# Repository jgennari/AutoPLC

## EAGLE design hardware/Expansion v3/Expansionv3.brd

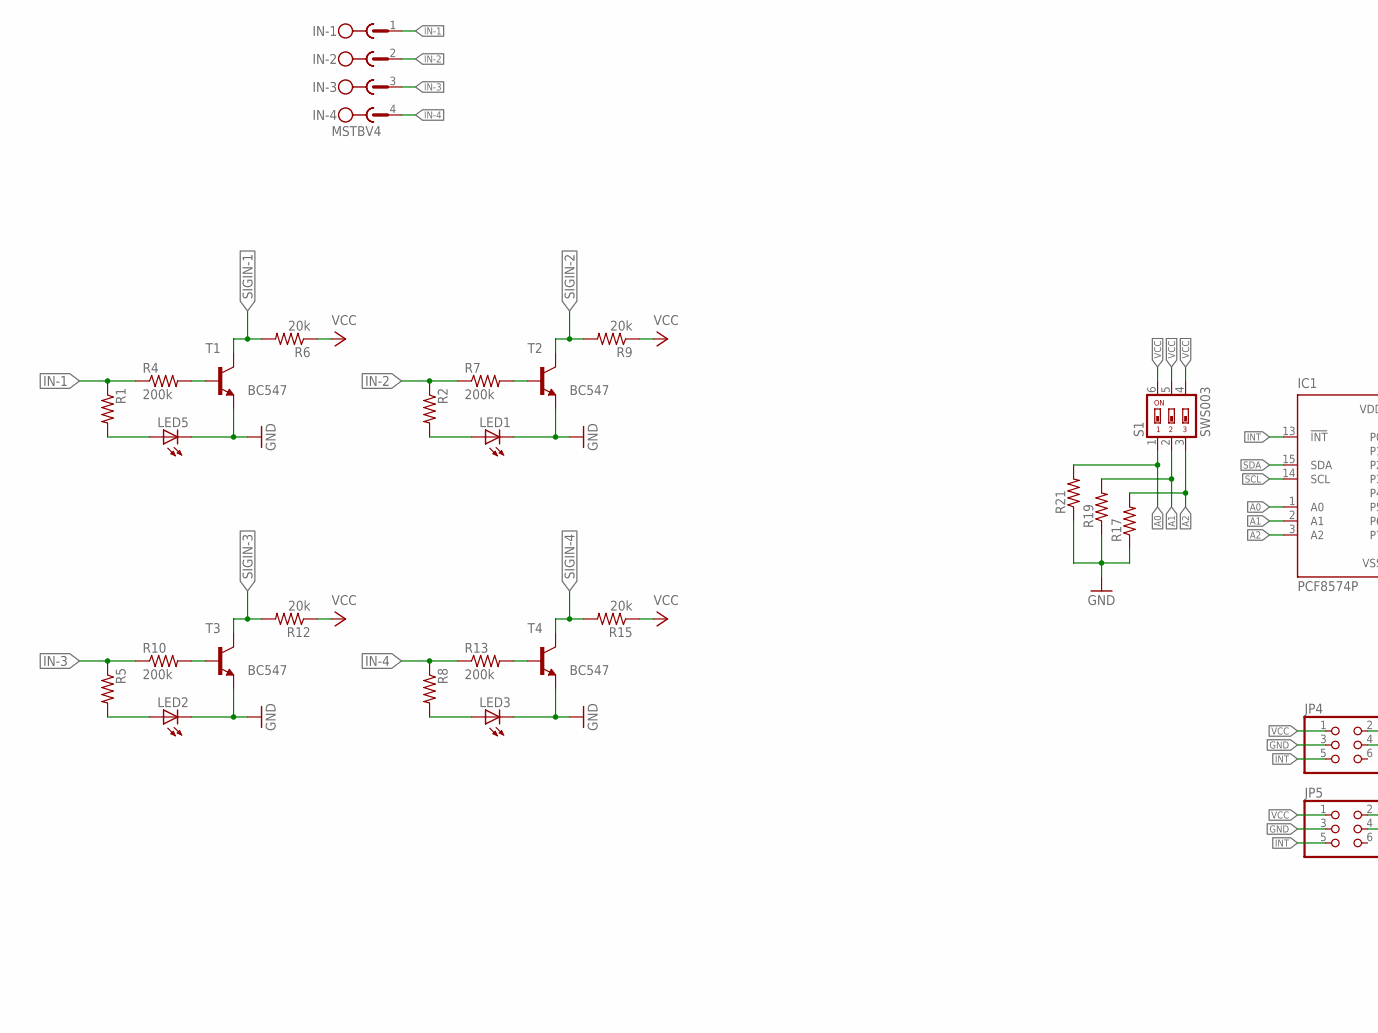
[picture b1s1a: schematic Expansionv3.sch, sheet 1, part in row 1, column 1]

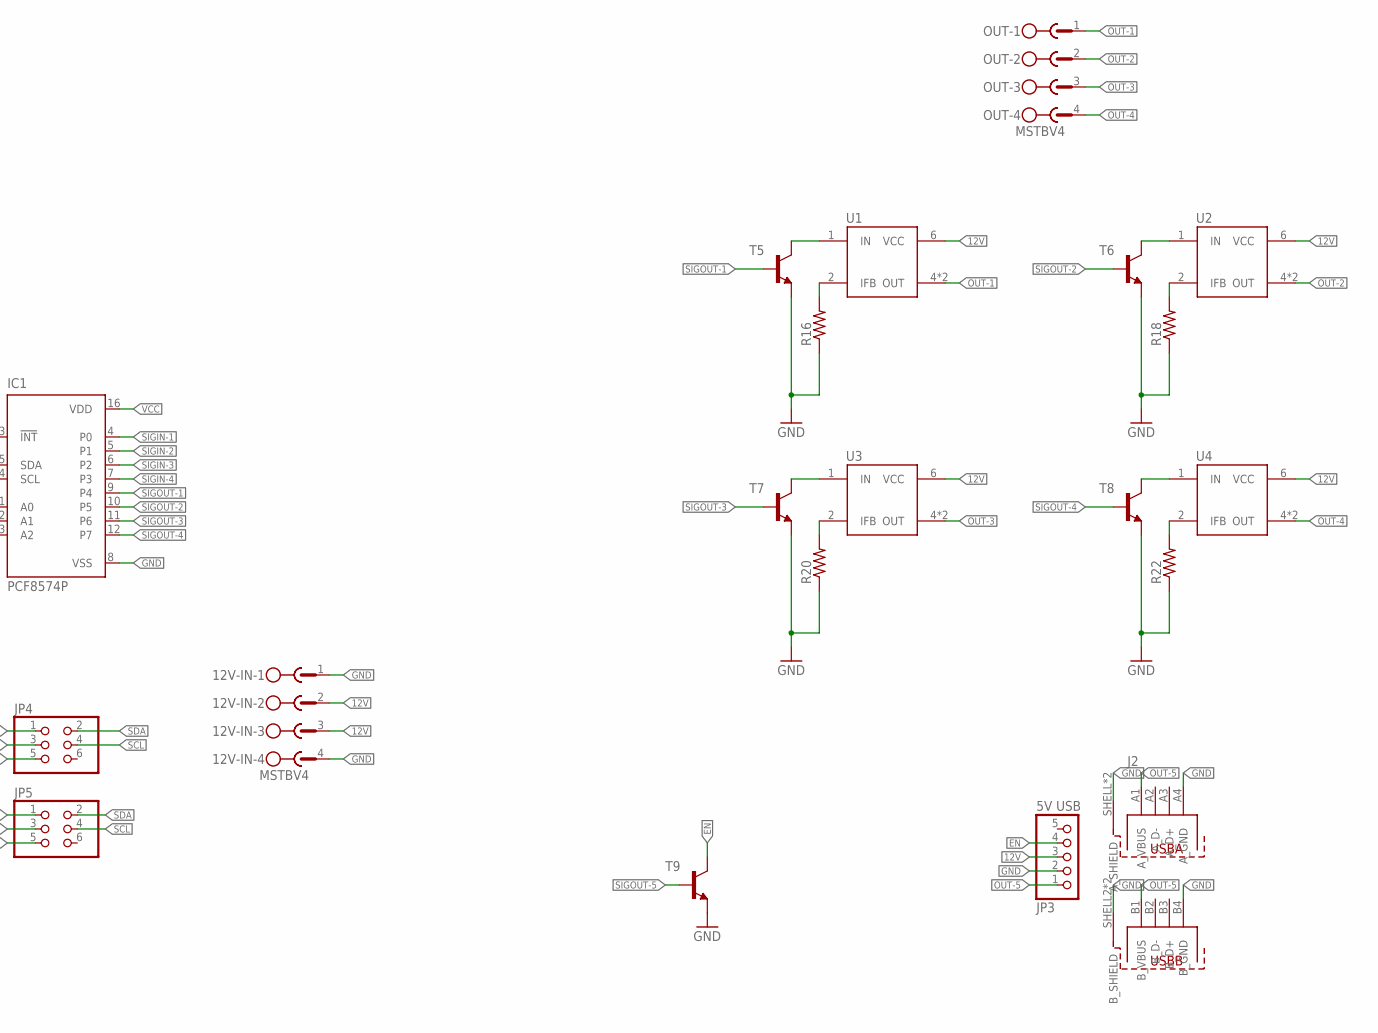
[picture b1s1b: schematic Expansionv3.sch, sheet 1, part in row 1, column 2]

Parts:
12V-IN: MSTBV4
IC1: PCF8574P; DIL16
IN: MSTBV4
J2: 614008235023
JP3: 5V USB; 1X05
JP4, JP5: PINHD-2X3; 2X03
LED1, LED2, LED3, LED5: LEDCHIPLED_0805; CHIPLED_0805
OUT: MSTBV4
R1, R2, R5, R8, R16, R17, R18, R19, R20, R21, R22: R-US_R0805; R0805
R4, R7, R10, R13: 200k; R0805
R6, R9, R12, R15: 20k; R0805
S1: SWS003; SMS-003
T1, T2, T3, T4: BC547; SOT23-EBC
T5, T6, T7, T8, T9: -NPN-SOT23-EBC; SOT23-EBC
U1, U2, U3, U4: IR3315; TO263-5

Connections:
12V: 12V-IN.2, 12V-IN.3, JP3.3, U1.6 (VCC), U2.6 (VCC), U3.6 (VCC), U4.6 (VCC)
A0: IC1.1 (A0), R21.2, S1.1
A1: IC1.2 (A1), R19.2, S1.2
A2: IC1.3 (A2), R17.2, S1.3
EN: JP3.4, T9.C
GND: 12V-IN.1, 12V-IN.4, IC1.8 (VSS), J2.A4 (A_GND), J2.B4 (B_GND), J2.SHELL (A_SHIELD), J2.SHELL1 (A_SHIELD), J2.SHELL2 (B_SHIELD), J2.SHELL3 (B_SHIELD), JP3.2, JP4.3, JP5.3, LED1.C, LED2.C, LED3.C, LED5.C, R16.1, R17.1, R18.1, R19.1, R20.1, R21.1, R22.1, T1.E, T2.E, T3.E, T4.E, T5.E, T6.E, T7.E, T8.E, T9.E
IN-1: IN.1, R1.1, R4.1
IN-2: IN.2, R2.1, R7.1
IN-3: IN.3, R5.1, R10.1
IN-4: IN.4, R8.1, R13.1
INT: IC1.13 (!INT), JP4.5, JP5.5
unnamed: LED5.A, R1.2
unnamed: R4.2, T1.B
unnamed: LED1.A, R2.2
unnamed: R7.2, T2.B
unnamed: LED2.A, R5.2
unnamed: R10.2, T3.B
unnamed: LED3.A, R8.2
unnamed: R13.2, T4.B
unnamed: T5.C, U1.1 (IN)
unnamed: R16.2, U1.2 (IFB)
unnamed: T6.C, U2.1 (IN)
unnamed: R18.2, U2.2 (IFB)
unnamed: T7.C, U3.1 (IN)
unnamed: R20.2, U3.2 (IFB)
unnamed: T8.C, U4.1 (IN)
unnamed: R22.2, U4.2 (IFB)
OUT-1: OUT.1, U1.4 (OUT), U1.5 (OUT)
OUT-2: OUT.2, U2.4 (OUT), U2.5 (OUT)
OUT-3: OUT.3, U3.4 (OUT), U3.5 (OUT)
OUT-4: OUT.4, U4.4 (OUT), U4.5 (OUT)
OUT-5: J2.A1 (A_VBUS), J2.B1 (B_VBUS), JP3.1
SCL: IC1.14 (SCL), JP4.4, JP5.4
SDA: IC1.15 (SDA), JP4.2, JP5.2
SIGIN-1: IC1.4 (P0), R6.2, T1.C
SIGIN-2: IC1.5 (P1), R9.2, T2.C
SIGIN-3: IC1.6 (P2), R12.2, T3.C
SIGIN-4: IC1.7 (P3), R15.2, T4.C
SIGOUT-1: IC1.9 (P4), T5.B
SIGOUT-2: IC1.10 (P5), T6.B
SIGOUT-3: IC1.11 (P6), T7.B
SIGOUT-4: IC1.12 (P7), T8.B
SIGOUT-5: T9.B
VCC: IC1.16 (VDD), JP4.1, JP5.1, R6.1, R9.1, R12.1, R15.1, S1.4, S1.5, S1.6

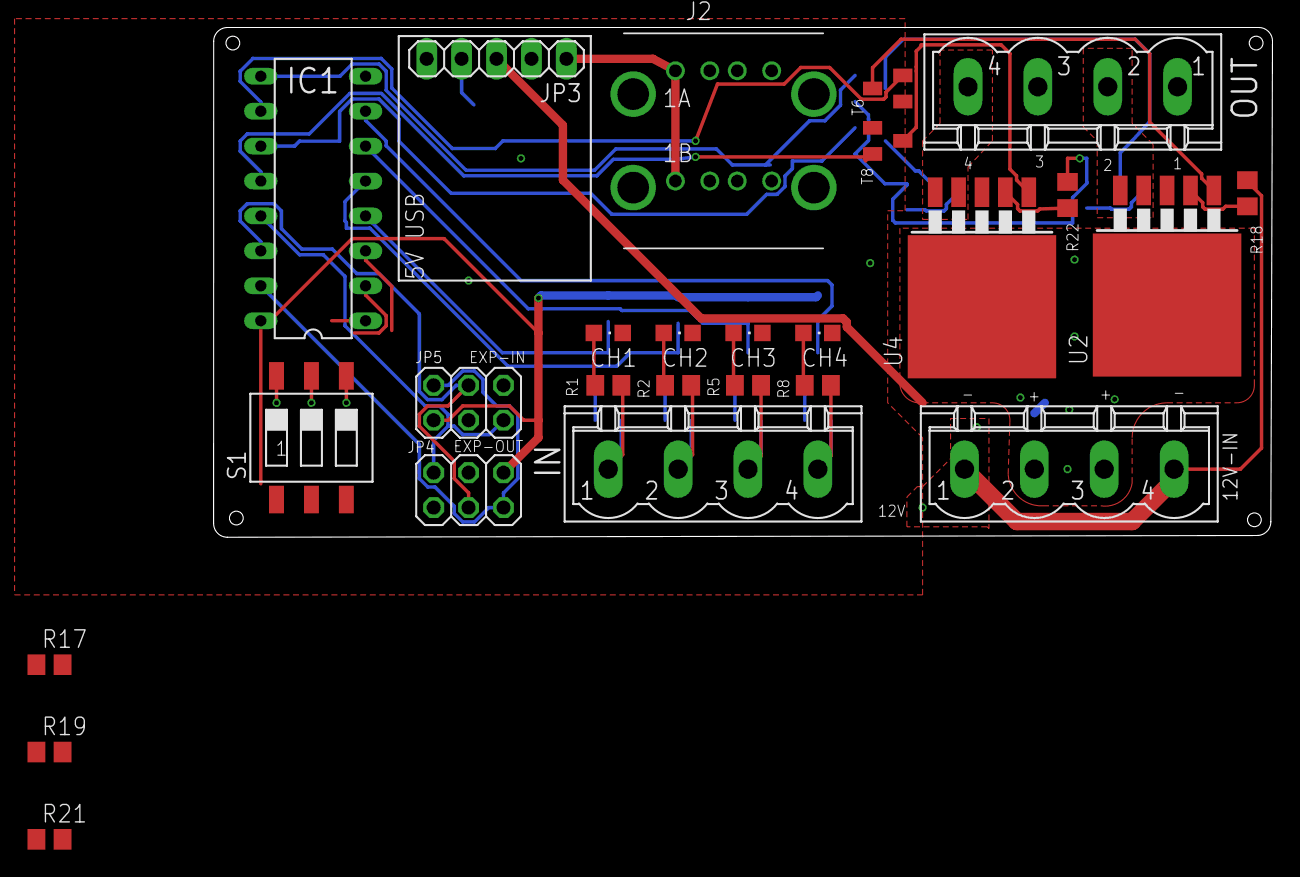
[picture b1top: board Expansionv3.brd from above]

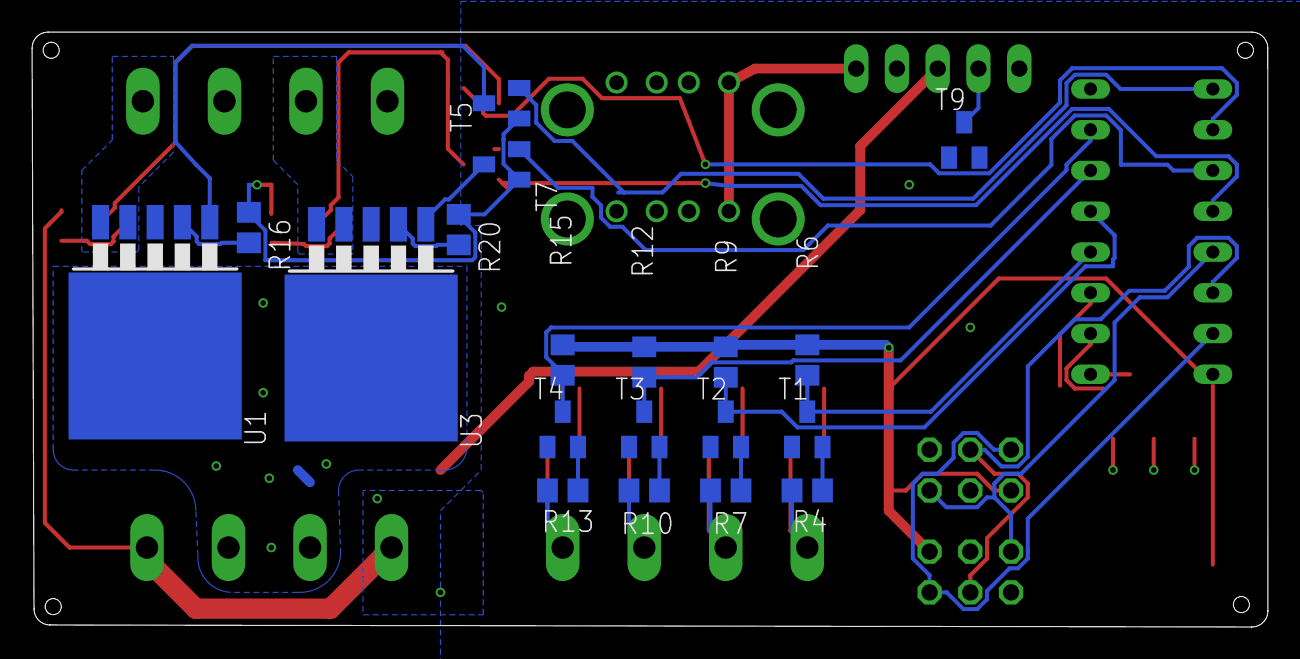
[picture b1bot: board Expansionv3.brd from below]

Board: 2 copper layers, 77.0 x 37.1 mm, 45 parts (19 on the bottom side), 43 nets.

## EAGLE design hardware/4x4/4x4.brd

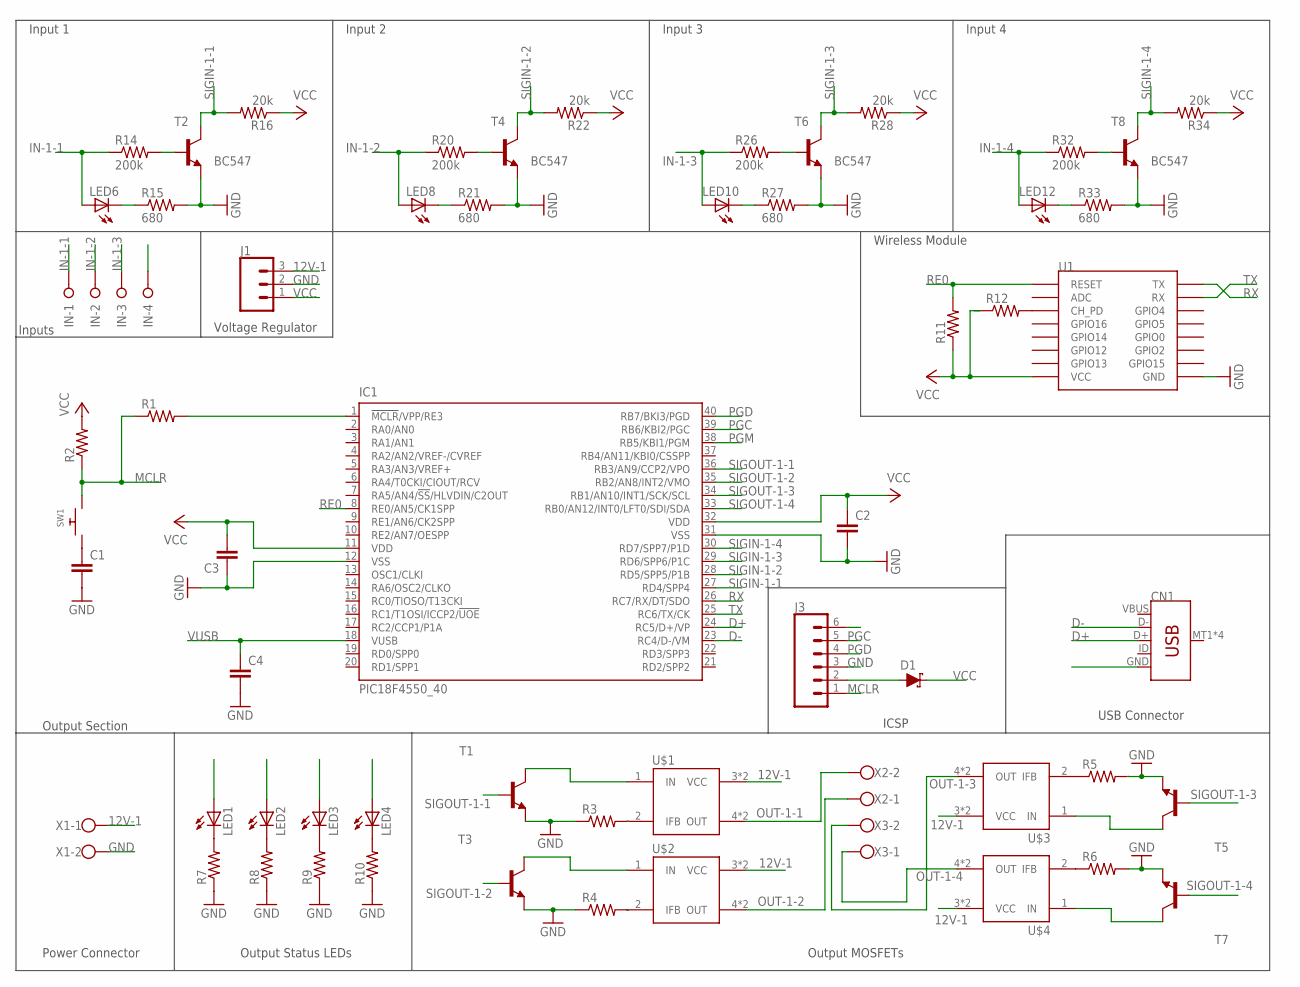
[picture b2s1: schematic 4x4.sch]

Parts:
C1, C2, C3, C4: C-EUC0805; C0805
CN1: USB_MICRO-B_SMT; USB-MICROB
D1: DIODE-SCHOTTKY-BAT20J; SOD-323
IC1: PIC18F4550_40; DIL40
IN: W237-04P; W237-4P
J1: CONN_03LONGPADS; 1X03_LONGPADS
J3: CONN_06LONGPADS; 1X06_LONGPADS
LED1, LED2, LED3, LED4, LED6, LED8, LED10, LED12: LEDCHIP-LED0805; CHIP-LED0805
R1, R2, R3, R4, R5, R6, R7, R8, R9, R10, R11, R12: R-US_R0805; R0805
R14, R20, R26, R32: 200k; R0805
R15, R21, R27, R33: 680; R0805
R16, R22, R28, R34: 20k; R0805
SW1: SWITCH_PUSHBUTTONSOFTTOUCHSMD_SJ; PUSHBUTTON_SMD_SJ
T1, T3, T5, T7: -NPN-SOT23-EBC; SOT23-EBC
T2, T4, T6, T8: BC547; SOT23-BEC
U1: ESP12SMD; ESP12-SMD
U$1, U$2, U$3, U$4: IR3315; TO-220-5
X1, X2, X3: W237-102

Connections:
12V-1: J1.3, U$1.3 (VCC), U$1.TAB (VCC), U$2.3 (VCC), U$2.TAB (VCC), U$3.3 (VCC), U$3.TAB (VCC), U$4.3 (VCC), U$4.TAB (VCC), X1.1
D+: CN1.D+, IC1.24 (RC5/D+/VP)
D-: CN1.D-, IC1.23 (RC4/D-/VM)
GND: C1.2, C2.2, C3.1, C4.2, CN1.GND, IC1.12 (VSS), IC1.31 (VSS), J1.2, J3.3, R3.1, R4.1, R5.2, R6.2, R7.1, R8.1, R9.1, R10.1, R15.2, R21.2, R27.2, R33.2, T1.E, T2.E, T3.E, T4.E, T5.E, T6.E, T7.E, T8.E, U1.GND, X1.2
IN-1-1: IN.1, LED6.A, R14.1
IN-1-2: IN.2, LED8.A, R20.1
IN-1-3: IN.3, LED10.A, R26.1
IN-1-4: IN.4, LED12.A, R32.1
MCLR: J3.1, R1.1, R2.1, SW1.P$1
unnamed: C1.1, SW1.P$2
unnamed: R3.2, U$1.2 (IFB)
unnamed: IC1.1 (!MCLR!/VPP/RE3), R1.2
unnamed: R5.1, U$3.2 (IFB)
unnamed: R6.1, U$4.2 (IFB)
unnamed: LED1.C, R7.2
unnamed: LED2.C, R8.2
unnamed: LED3.C, R9.2
unnamed: LED4.C, R10.2
unnamed: R12.2, U1.CH_PD
unnamed: R14.2, T2.B
unnamed: LED6.C, R15.1
unnamed: R4.2, U$2.2 (IFB)
unnamed: R20.2, T4.B
unnamed: LED8.C, R21.1
unnamed: D1.A, J3.2
unnamed: R26.2, T6.B
unnamed: LED10.C, R27.1
unnamed: R32.2, T8.B
unnamed: LED12.C, R33.1
OUT2: T3.C, U$2.1 (IN)
OUT3: T5.C, U$3.1 (IN)
OUT4: T7.C, U$4.1 (IN)
OUT-1-1: LED1.A, U$1.4 (OUT), U$1.5 (OUT), X2.2
OUT-1-2: LED2.A, U$2.4 (OUT), U$2.5 (OUT), X2.1
OUT-1-3: LED3.A, U$3.4 (OUT), U$3.5 (OUT), X3.2
OUT-1-4: LED4.A, U$4.4 (OUT), U$4.5 (OUT), X3.1
PGC: IC1.39 (RB6/KBI2/PGC), J3.5
PGD: IC1.40 (RB7/BKI3/PGD), J3.4
PGM: IC1.38 (RB5/KBI1/PGM)
RE0: IC1.8 (RE0/AN5/CK1SPP), R11.2, U1.RESET
RX: IC1.26 (RC7/RX/DT/SDO), U1.TXD0 (TX)
SIG1: T1.C, U$1.1 (IN)
SIGIN-1-1: IC1.27 (RD4/SPP4), R16.2, T2.C
SIGIN-1-2: IC1.28 (RD5/SPP5/P1B), R22.2, T4.C
SIGIN-1-3: IC1.29 (RD6/SPP6/P1C), R28.2, T6.C
SIGIN-1-4: IC1.30 (RD7/SPP7/P1D), R34.2, T8.C
SIGOUT-1-1: IC1.36 (RB3/AN9/CCP2/VPO), T1.B
SIGOUT-1-2: IC1.35 (RB2/AN8/INT2/VMO), T3.B
SIGOUT-1-3: IC1.34 (RB1/AN10/INT1/SCK/SCL), T5.B
SIGOUT-1-4: IC1.33 (RB0/AN12/INT0/LFT0/SDI/SDA), T7.B
TX: IC1.25 (RC6/TX/CK), U1.RXD0 (RX)
VBUS: CN1.VBUS
VCC: C2.1, C3.2, D1.C, IC1.11 (VDD), IC1.32 (VDD), J1.1, R2.2, R11.1, R12.1, R16.1, R22.1, R28.1, R34.1, U1.VCC
VUSB: C4.1, IC1.18 (VUSB)

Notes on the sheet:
Output Section
Power Connector
Output Status LEDs
Output MOSFETs
USB Connector
Input 1
Input 2
Input 3
Input 4
Inputs
Wireless Module
Voltage Regulator
ICSP

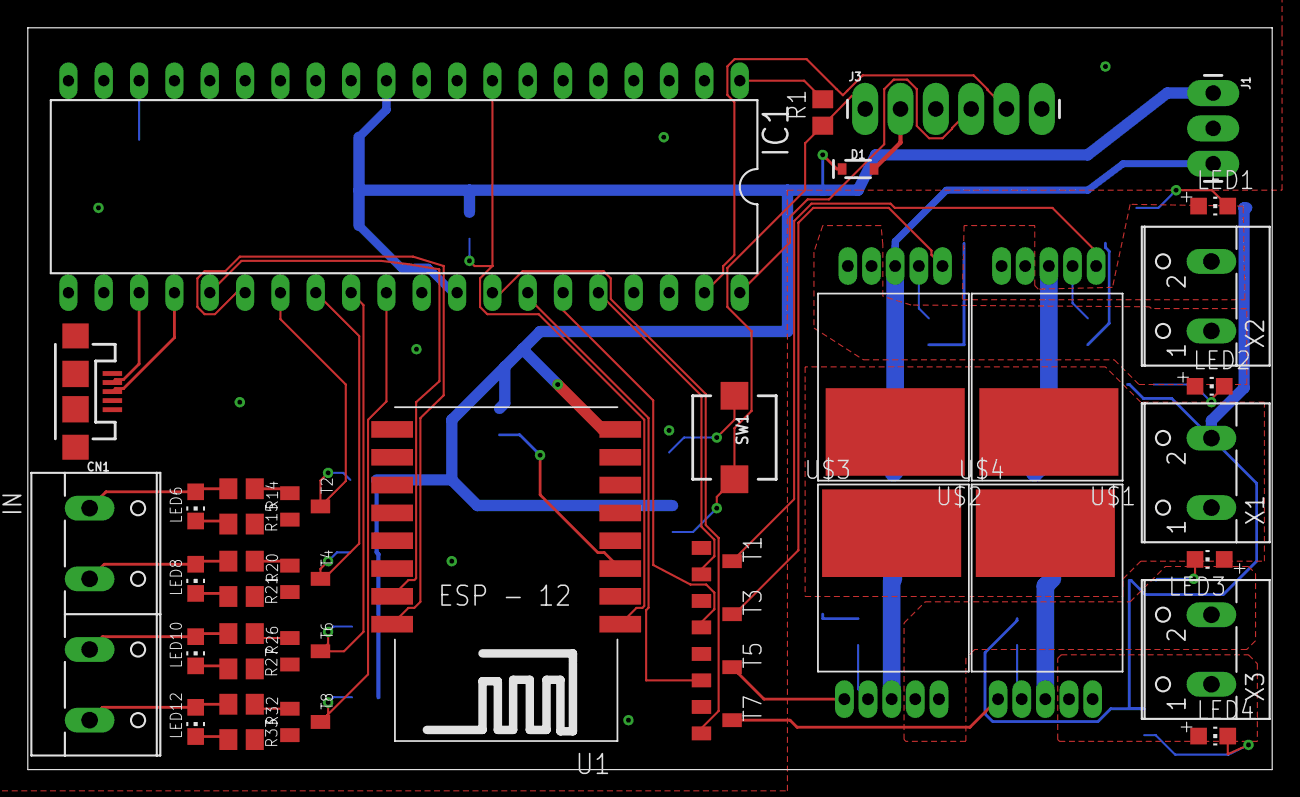
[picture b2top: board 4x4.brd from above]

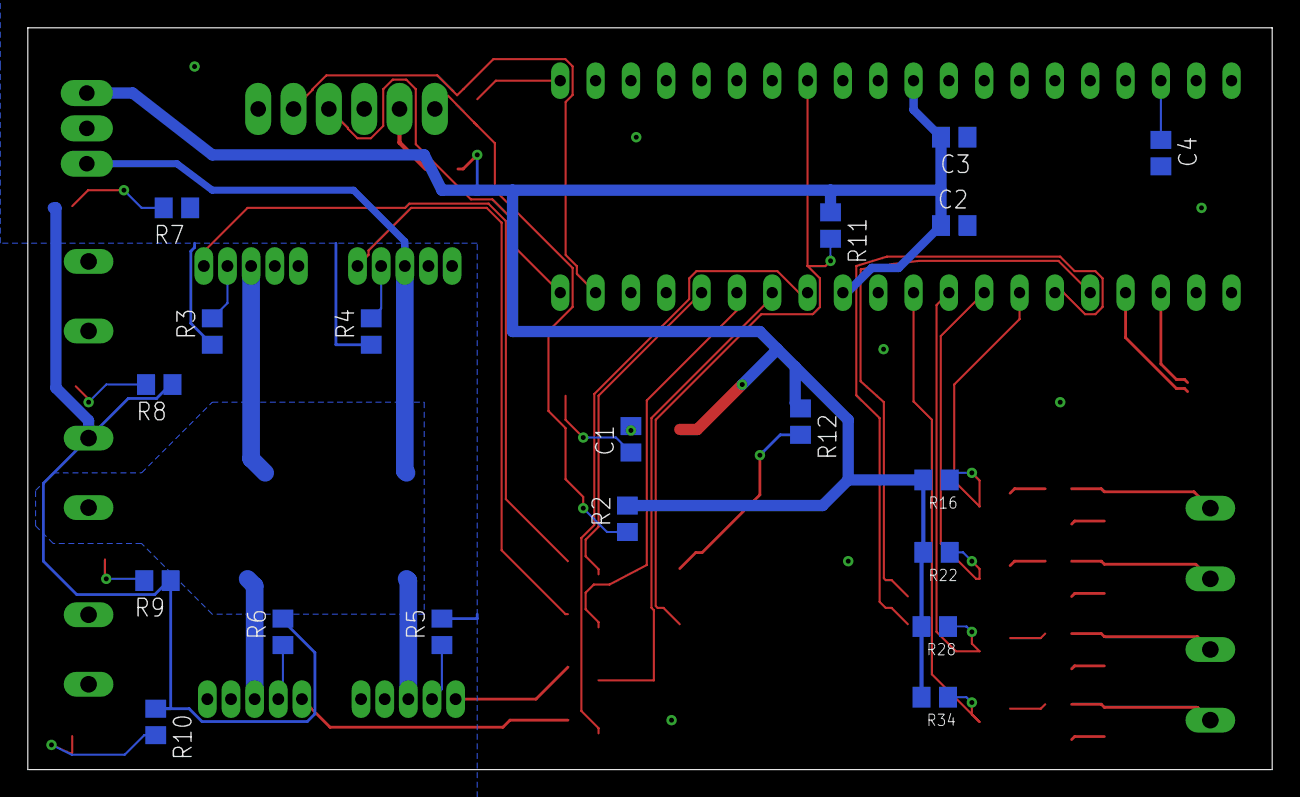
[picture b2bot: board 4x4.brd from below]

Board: 2 copper layers, 89.5 x 53.3 mm, 59 parts (19 on the bottom side), 52 nets.

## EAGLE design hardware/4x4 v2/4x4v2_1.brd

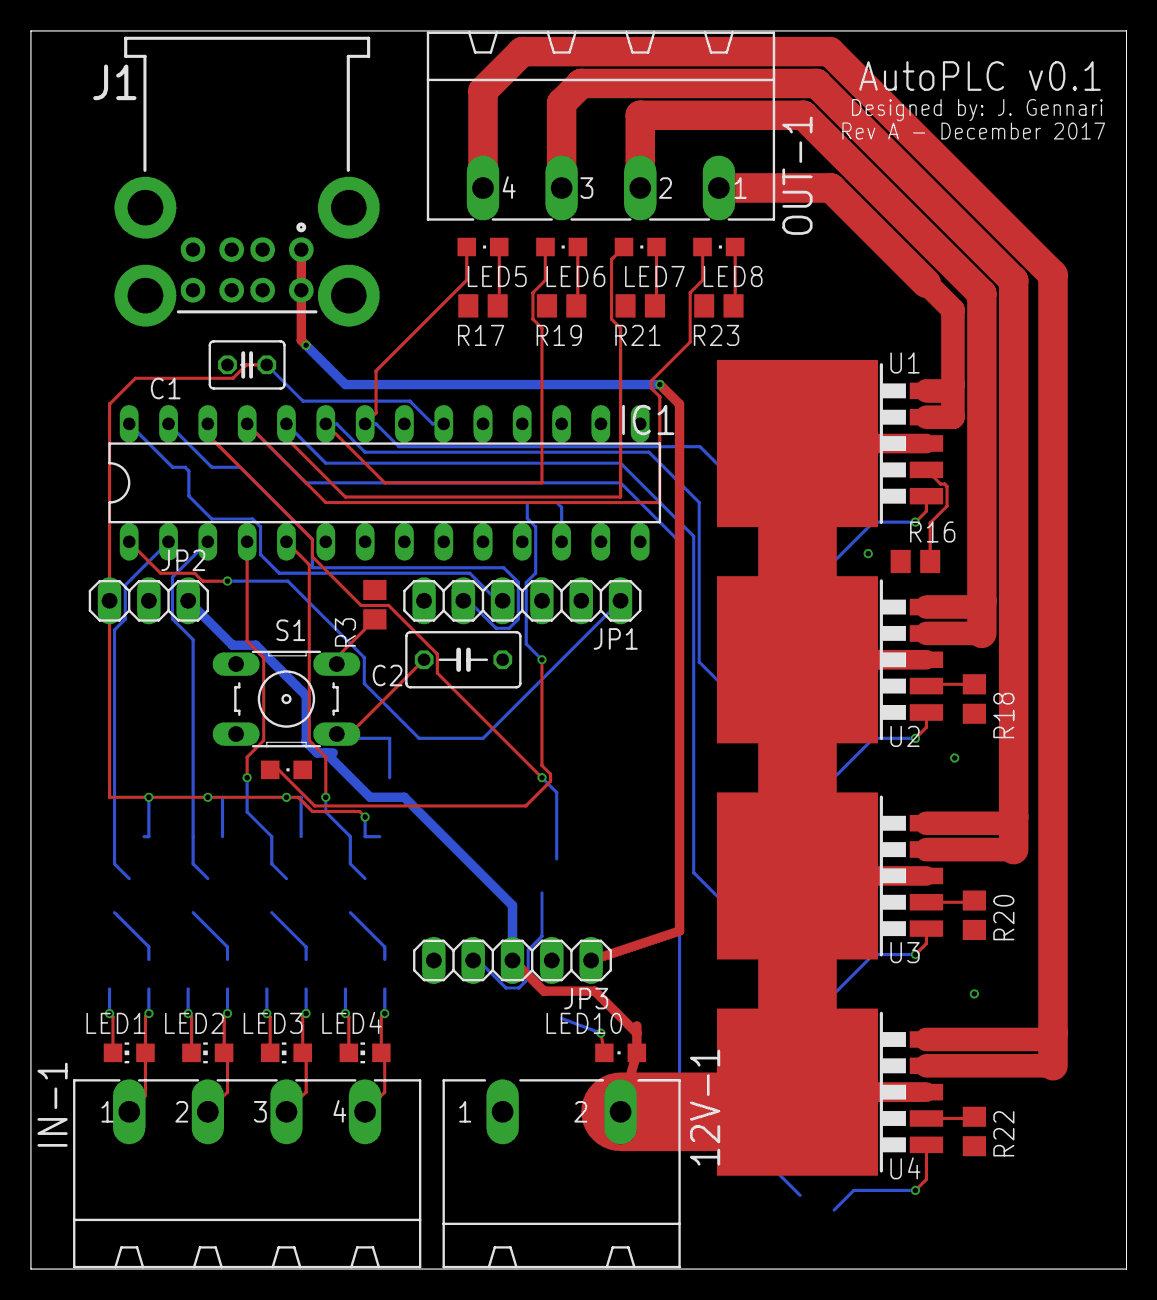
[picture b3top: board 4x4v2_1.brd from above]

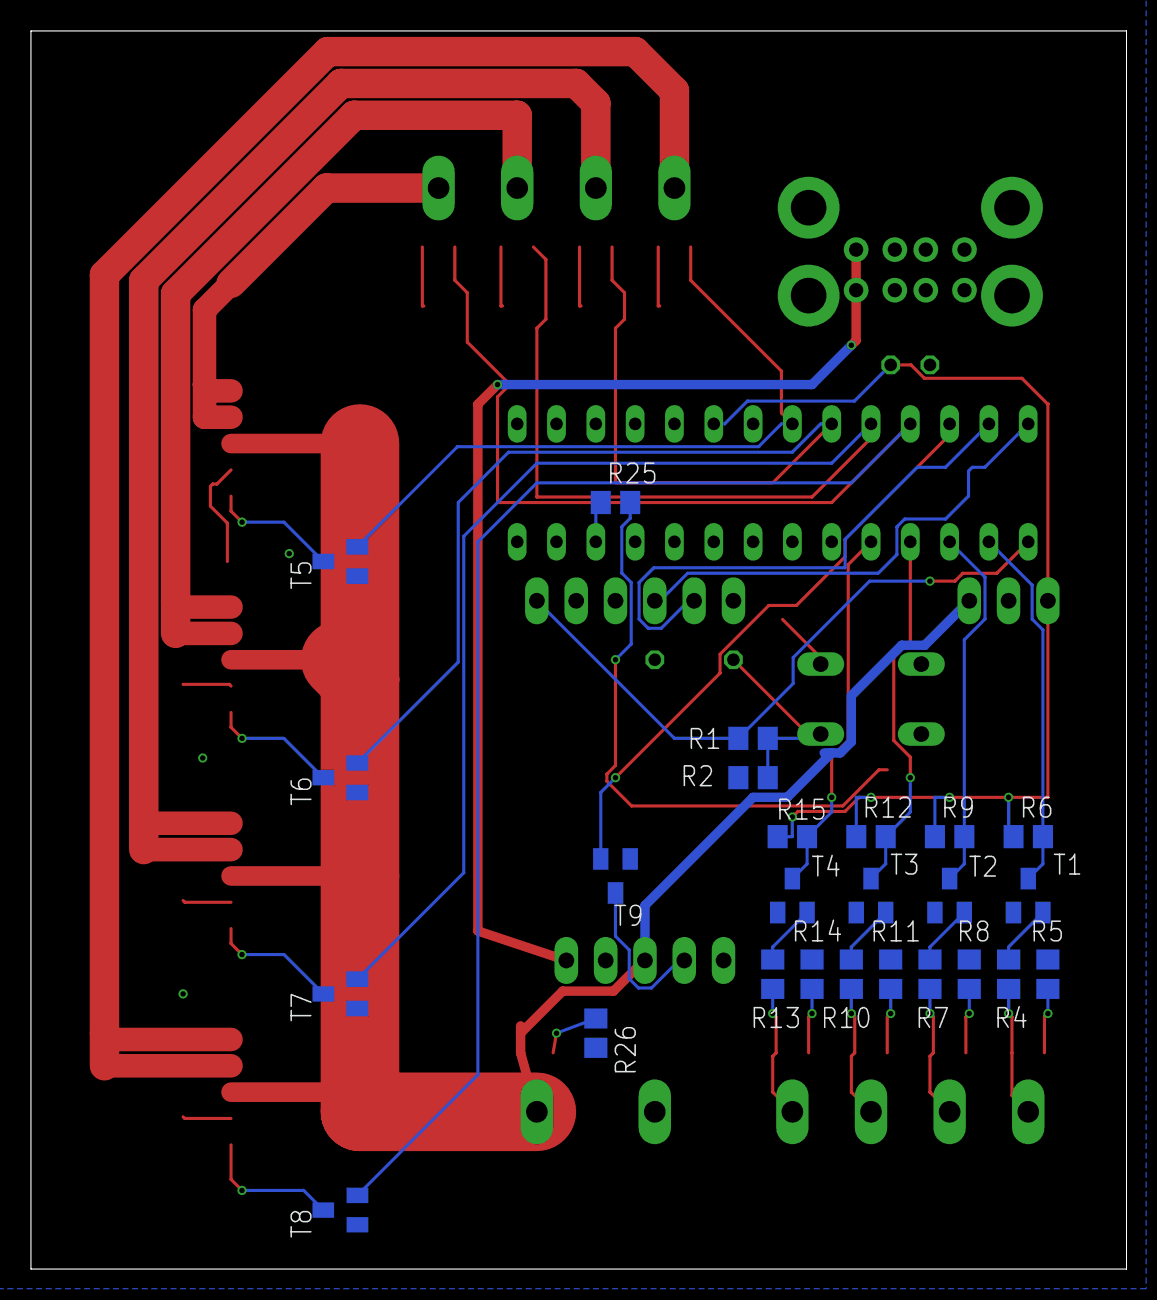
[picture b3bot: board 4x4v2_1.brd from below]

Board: 2 copper layers, 70.8 x 80.0 mm, 59 parts (25 on the bottom side), 50 nets.

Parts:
12V-1: GMSTBA2
C1: C025-030X050
C2: C050-035X075
IC1: PIC18F2480-I/SP; DIL28-3
IN-1: MSTBA4
J1: USB1035-XX-X-X-X-B_REVE; GCT_USB1035-XX-X-X-X-B_REVE
JP1: 1X06
JP2: 1X03
JP3: 1X05
LED1: 12123; CHIP-LED0805
LED2, LED3, LED4: CHIP-LED0805
LED5, LED6, LED7, LED8, LED10: CHIPLED_0805
LED9: STATUS; CHIPLED_0805
OUT-1: MSTBA4
R1, R2, R3, R16, R17, R18, R19, R20, R21, R22, R23, R25, R26: R0805
R4, R7, R10, R13: 200k; R0805
R5, R8, R11, R14: 680; R0805
R6, R9, R12, R15: 20k; R0805
S1: B3F-10XX
T1, T2, T3, T4: BC547; SOT23-EBC
T5, T6, T7, T8, T9: SOT23-EBC
U1, U2, U3, U4: IR3315; TO263-5

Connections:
12V-1: 12V-1.2, JP2.1, JP3.3, LED10.A, U1.3, U1.6, U2.3, U2.6, U3.3, U3.6, U4.3, U4.6
EN: JP3.4, T9.C
GND: 12V-1.1, C1.2, C2.2, IC1.8, IC1.19, J1.4A, J1.4B, J1.9, J1.10, J1.11, J1.12, JP1.3, JP2.2, JP3.2, LED9.C, R3.1, R5.2, R8.2, R11.2, R14.2, R16.1, R17.1, R18.1, R19.1, R20.1, R21.1, R22.1, R23.1, R26.2, T1.E, T2.E, T3.E, T4.E, T5.E, T6.E, T7.E, T8.E, T9.E
IN-1-1: IN-1.1, LED1.A, R4.1
IN-1-2: IN-1.2, LED2.A, R7.1
IN-1-3: IN-1.3, LED3.A, R10.1
IN-1-4: IN-1.4, LED4.A, R13.1
MCLR: IC1.1, JP1.1, R1.1
unnamed: C2.1, R1.2, R2.1, S1.1
unnamed: R3.2, S1.3
unnamed: R4.2, T1.B
unnamed: LED1.C, R5.1
unnamed: R7.2, T2.B
unnamed: LED2.C, R8.1
unnamed: R10.2, T3.B
unnamed: LED3.C, R11.1
unnamed: R13.2, T4.B
unnamed: LED4.C, R14.1
unnamed: T5.C, U1.1
unnamed: R16.2, U1.2
unnamed: LED5.C, R17.2
unnamed: T6.C, U2.1
unnamed: R18.2, U2.2
unnamed: LED6.C, R19.2
unnamed: T7.C, U3.1
unnamed: R20.2, U3.2
unnamed: LED7.C, R21.2
unnamed: T8.C, U4.1
unnamed: R22.2, U4.2
unnamed: LED8.C, R23.2
unnamed: LED9.A, R25.2
unnamed: LED10.C, R26.1
OUT-1-1: OUT-1.1, U1.4, U1.5
OUT-1-2: OUT-1.2, U2.4, U2.5
OUT-1-3: OUT-1.3, U3.4, U3.5
OUT-1-4: OUT-1.4, U4.4, U4.5
OUT-1-5: J1.1A, J1.1B, JP3.1
PGC: IC1.27, JP1.5
PGD: IC1.28, JP1.4
SIGIN-1-1: IC1.2, R6.2, T1.C
SIGIN-1-2: IC1.3, R9.2, T2.C
SIGIN-1-3: IC1.4, R12.2, T3.C
SIGIN-1-4: IC1.5, R15.2, T4.C
SIGOUT-1-1: IC1.22, LED5.A, T5.B
SIGOUT-1-2: IC1.23, LED6.A, T6.B
SIGOUT-1-3: IC1.24, LED7.A, T7.B
SIGOUT-1-4: IC1.25, LED8.A, T8.B
SIGOUT-1-5: IC1.26, T9.B
STATUS_LED: IC1.12, R25.1
VCC: C1.1, IC1.20, JP2.3, R6.1, R9.1, R12.1, R15.1

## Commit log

2017-12-30 Added ext board

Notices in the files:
parts and their libraries:
SparkFun-Connectors: Licensing: Creative Commons ShareAlike 4.0 International - https://creativecommons.org/licenses/by-sa/4.0
InputOutputIO: Copyright: Würth Elektronik
